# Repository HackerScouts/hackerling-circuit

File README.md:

hackerling-circuit
==================

Development in this Repo is closed.. continued work on the Hackerling Circuit can be found -> https://github.com/CuriosityHacked/hackerling-circuit

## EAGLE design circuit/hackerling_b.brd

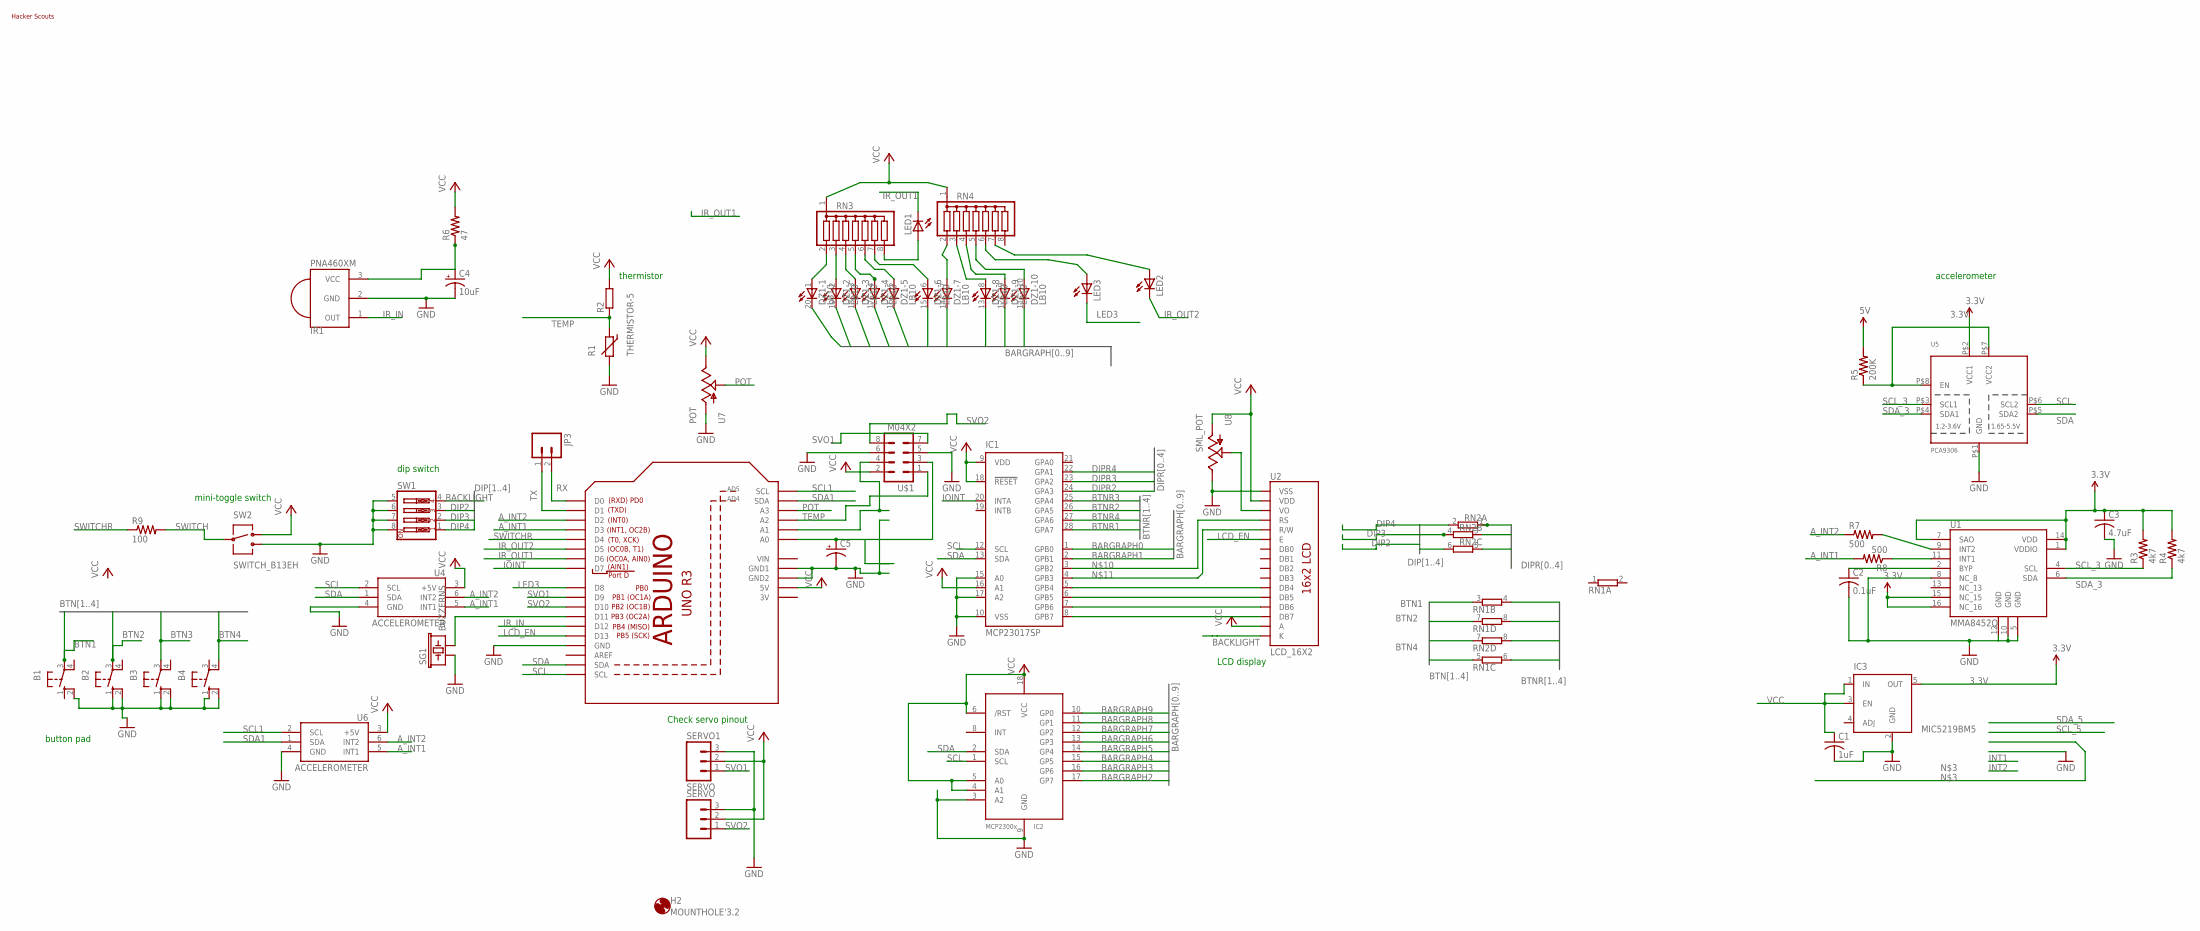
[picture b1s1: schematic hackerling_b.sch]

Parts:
B1, B2, B3, B4: SWITCH_BCF-4000; SWITCH_B3F-4000
C1: 1uF; C0603K
C2: 0.1uF; C0603K
C3: 4.7uF; C0603K
C4: 10uF; CAP_050X075
C5: CPOL-USE5-4; E5-4
DZ1: LB10
H2: MOUNTHOLE'3.2; HOLE_3.2
HACKERSCOUTSLOGO: HS-LOGO; HS-LOGO-SM-NOTEXT
IC1: MCP23017SP; DIL28-3
IC2: MCP2300X/P; DIL18
IC3: MIC5219BM5; SOT23-5
IR1: PNA460XM
JP3: M02LOCK; 1X02_LOCK
LED1, LED2, LED3: LED5MM
R1: THERMISTOR-5; R-5
R2: R-EU_0204/7; 0204/7
R3, R4: 4k7; 0603-RES
R5: 200K; 0603-RES
R6: 47; 0204/7
R7, R8: 500; 0603-RES
R9: 100; 0204/7
RN1, RN2: E4R; SIL8
RN3, RN4: G07R; SIL8
SERVO: M03LOCK; 1X03_LOCK
SERVO1: SERVO; 1X03_LOCK
SG1: BUZZERNS; BUZZER-12MM-NS
SW1: SW_DIP-4; EDG-04
SW2: SWITCH_B13EH
U1: MMA8452Q; QFN-16(5X3)
U2: LCD_16X2
U3: ARDUINOR3-BPLACE
U4, U6: ACCELEROMETER
U5: PCA9306; VSSOP-8
U7: POT; ALS_POT
U8: SML_POT
U$1: M04X2; 2X4

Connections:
3.3V: C3.1, IC3.5 (OUT), R3.2, R4.2, U1.1 (VDDIO), U1.7 (SAO), U1.14 (VDD), U1.15 (NC_15), U1.16 (NC_16), U5.P$2 (VCC1)
3V: U3.3V
A_INT1: R8.2, U3.D3, U4.5 (INT1), U6.5 (INT1)
A_INT2: R7.1, U3.D2, U4.6 (INT2), U6.6 (INT2)
BACKLIGHT: SW1.4, U2.16 (K)
BARGRAPH0: DZ1.20 (C), IC1.1 (GPB0)
BARGRAPH1: DZ1.19 (C), IC1.2 (GPB1)
BARGRAPH2: DZ1.18 (C), IC2.17 (GP7)
BARGRAPH3: DZ1.17 (C), IC2.16 (GP6)
BARGRAPH4: DZ1.16 (C), IC2.15 (GP5)
BARGRAPH5: DZ1.15 (C), IC2.14 (GP4)
BARGRAPH6: DZ1.14 (C), IC2.13 (GP3)
BARGRAPH7: DZ1.13 (C), IC2.12 (GP2)
BARGRAPH8: DZ1.12 (C), IC2.11 (GP1)
BARGRAPH9: DZ1.11 (C), IC2.10 (GP0)
BTN1: B1.3, RN1.3 (1)
BTN2: B2.3, RN1.7 (1)
BTN3: B3.3, RN2.7 (1)
BTN4: B4.4 (P1), RN1.5 (1)
BTNR1: IC1.28 (GPA7), RN1.4 (2)
BTNR2: IC1.26 (GPA5), RN1.8 (2)
BTNR3: IC1.25 (GPA4), RN2.8 (2)
BTNR4: IC1.27 (GPA6), RN1.6 (2)
DIP2: RN2.6 (2), SW1.3
DIP3: RN2.4 (2), SW1.2
DIP4: RN2.2, SW1.1
DIPR2: IC1.24 (GPA3), RN2.5 (1)
DIPR3: IC1.23 (GPA2), RN2.3 (1)
DIPR4: IC1.22 (GPA1), RN2.1
GND: B1.2 (S1), B2.1 (S), B2.2 (S1), B3.1 (S), B3.2 (S1), B4.1 (S), B4.2 (S1), C1.2, C2.2, C3.2, C4.2 (-), C5.-, IC1.10 (VSS), IC1.15 (A0), IC1.17 (A2), IC2.3 (A2), IC2.9 (GND), IC3.2 (GND), IR1.2 (GND), R1.2, SERVO.3, SERVO1.3, SG1.+ (1), SW1.5, SW1.6, SW1.7, SW1.8, SW2.3, U1.5 (GND), U1.8 (NC_8), U1.10 (GND), U1.12 (GND), U2.1 (VSS), U2.B1 (VSS), U3.GND, U3.GND1, U3.GND2, U4.4 (GND), U5.P$1 (GND), U6.4 (GND), U7.P$1 (A), U8.E, U$1.5, U$1.6
IOINT: IC1.20 (INTA), U3.D7
IR_IN: IR1.1 (OUT), U3.D12
IR_OUT1: LED1.K (C), U3.D6
IR_OUT2: LED2.K (C), U3.D5
LCD_EN: U2.6 (E), U3.D13
LED3: LED3.K (C), U3.D8
unnamed: IC1.8 (GPB7), U2.14 (DB7)
unnamed: IC1.7 (GPB6), U2.13 (DB6), U2.B13 (DB6)
unnamed: IC1.6 (GPB5), U2.12 (DB5), U2.B12 (DB5)
unnamed: IC1.5 (GPB4), U2.11 (DB4)
unnamed: R5.1, U5.P$7 (VCC2), U5.P$8 (EN)
unnamed: R7.2, U1.9 (INT2)
unnamed: R8.1, U1.11 (INT1)
unnamed: DZ1.2 (A), RN3.3
unnamed: DZ1.3 (A), RN3.4
unnamed: IC1.3 (GPB2), U2.4 (RS)
unnamed: IC1.4 (GPB3), U2.5 (R/W)
unnamed: LED2.A, RN4.7
unnamed: U2.3 (VO), U8.S
unnamed: SG1.- (2), U3.D11
unnamed: DZ1.7 (A), RN4.2
unnamed: DZ1.6 (A), RN3.7
unnamed: DZ1.1 (A), RN3.2
unnamed: C4.1 (+), IR1.3 (VCC), R6.1
unnamed: LED3.A, RN4.6
unnamed: DZ1.4 (A), RN3.5
unnamed: DZ1.5 (A), RN3.6
unnamed: U3.A1, U$1.4
unnamed: C2.1, U1.2 (BYP)
unnamed: C5.+, U3.A0, U$1.3
unnamed: DZ1.8 (A), RN4.3
unnamed: DZ1.9 (A), RN4.4
unnamed: DZ1.10 (A), RN4.5
unnamed: LED1.A, RN3.8
POT: U3.A3, U7.P$2 (S)
RX: JP3.2, U3.D0
SCL: IC1.12 (SCL), IC2.1 (SCL), U3.SCL, U4.2 (SCL), U5.P$6 (SCL2)
SCL1: U3.A5 (SCL), U6.2 (SCL)
SCL_3: R3.1, U1.4 (SCL), U5.P$3 (SCL1)
SDA: IC1.13 (SDA), IC2.2 (SDA), U3.SDA, U4.1 (SDA), U5.P$5 (SDA2)
SDA1: U3.A4 (SDA), U6.1 (SDA)
SDA_3: R4.1, U1.6 (SDA), U5.P$4 (SDA1)
SVO1: SERVO1.1, U3.D9, U$1.7
SVO2: SERVO.1, U3.D10, U$1.8
SWITCH: R9.2, SW2.2
SWITCHR: R9.1, U3.D4
TEMP: R1.1, R2.1, U3.A2, U$1.1
TX: JP3.1, U3.D1
VCC: C1.1, IC1.9 (VDD), IC1.16 (A1), IC1.18 (!RESET), IC2.4 (A1), IC2.5 (A0), IC2.6 (/RST), IC2.18 (VCC), IC3.1 (IN), IC3.3 (EN), R2.2, R5.2, R6.2, RN3.1, RN4.1, SERVO.2, SERVO1.2, SW2.1, U2.2 (VDD), U2.15 (A), U2.B2 (VDD), U3.5V, U4.3 (+5V), U6.3 (+5V), U7.P$3 (E), U8.A, U$1.2
VIN: U3.VIN

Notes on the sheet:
mini-toggle switch
thermistor
dip switch
LCD display
button pad
accelerometer
Check servo pinout

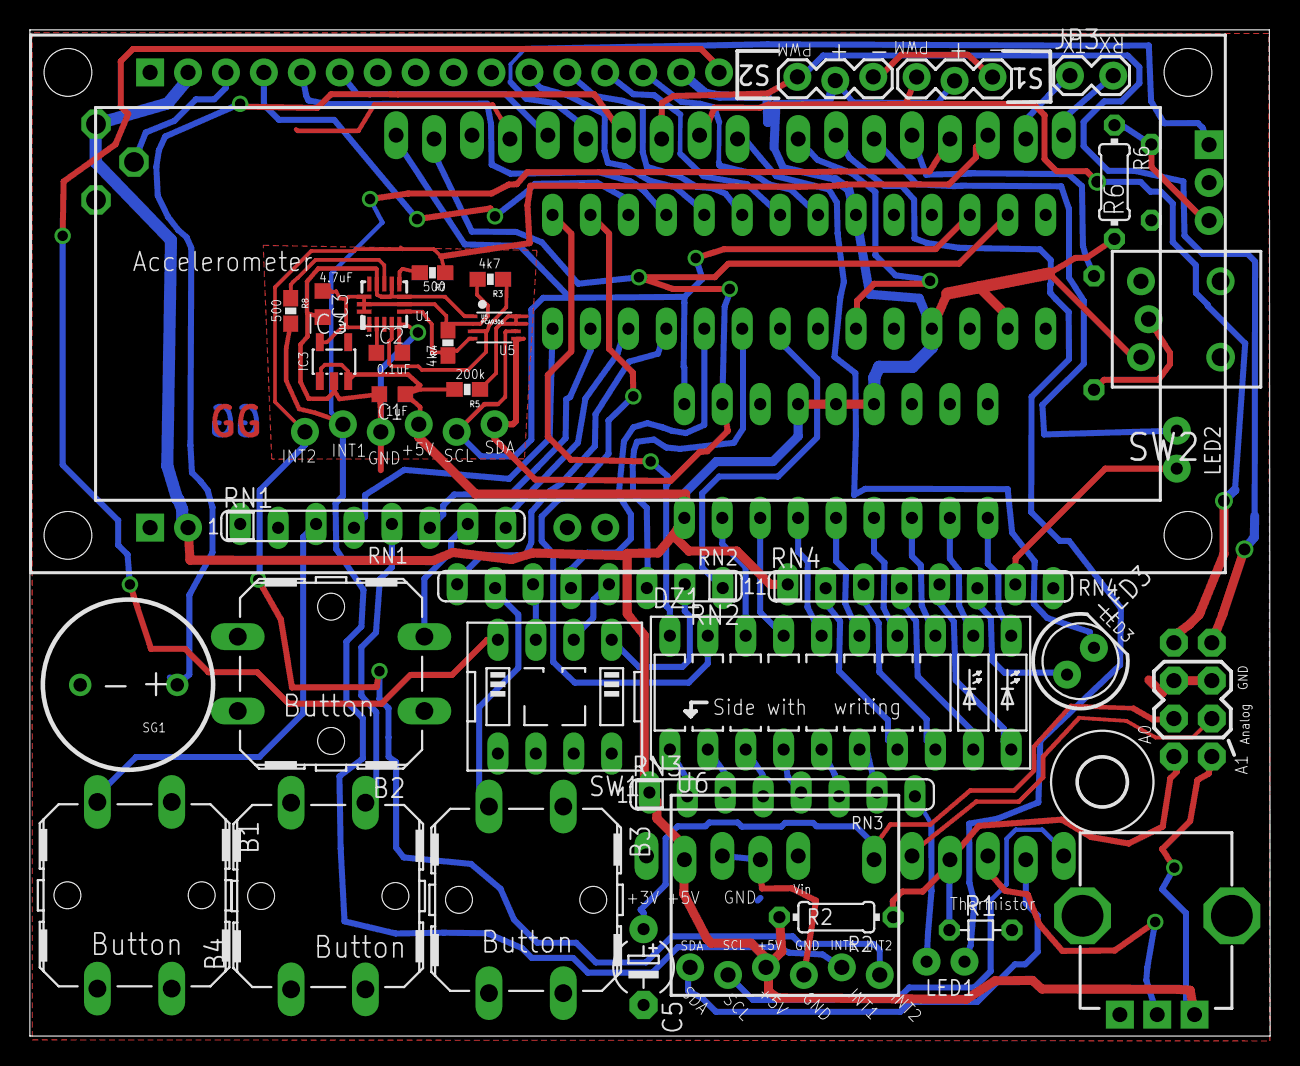
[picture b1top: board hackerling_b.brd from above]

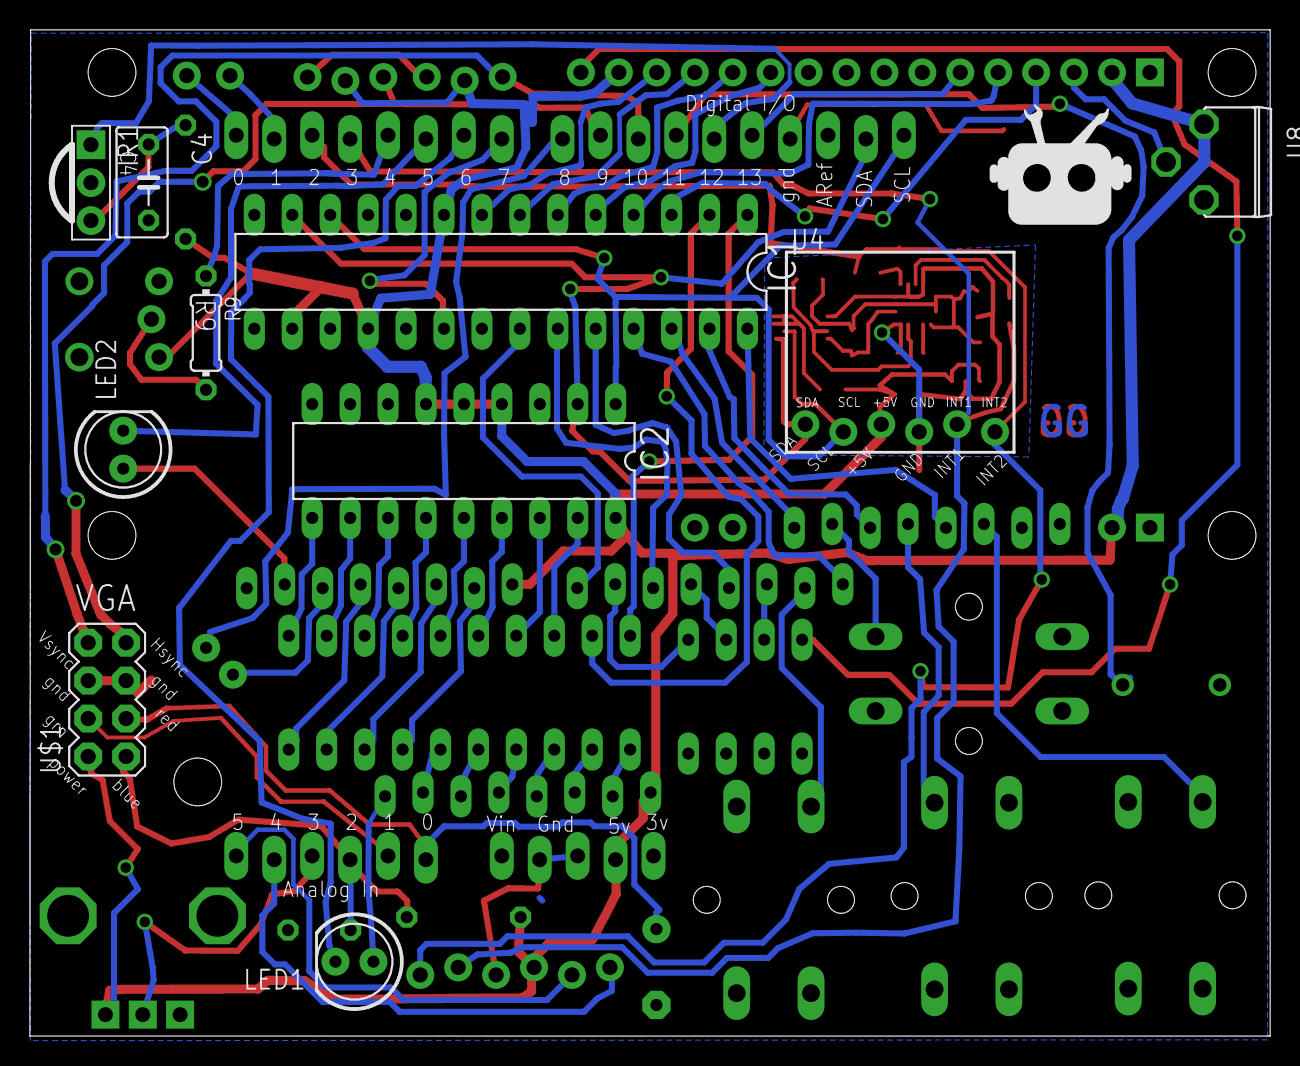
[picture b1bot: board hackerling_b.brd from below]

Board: 2 copper layers, 83.1 x 67.4 mm, 47 parts (11 on the bottom side), 78 nets.

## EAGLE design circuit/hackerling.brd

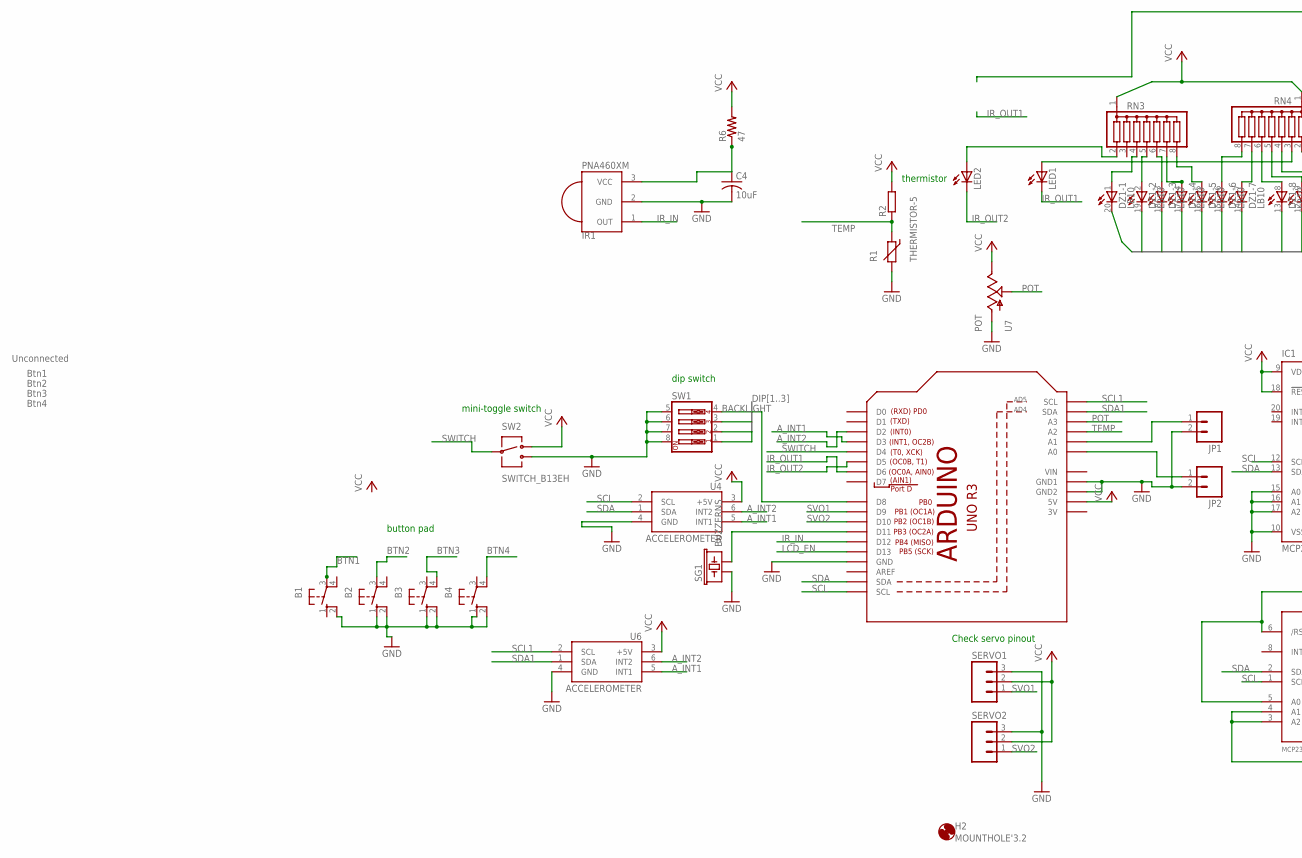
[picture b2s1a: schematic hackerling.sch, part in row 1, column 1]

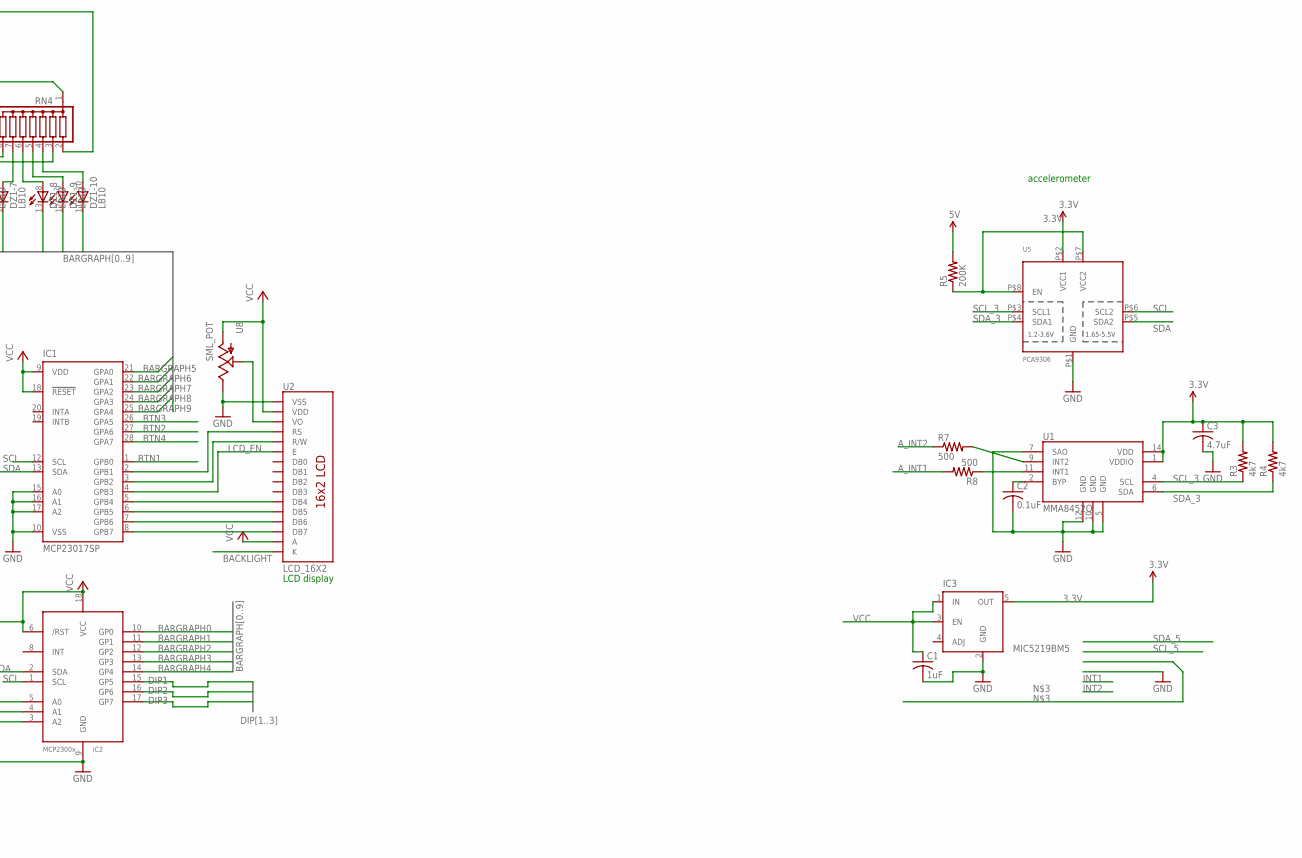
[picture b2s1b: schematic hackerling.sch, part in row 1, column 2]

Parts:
B1, B2, B3, B4: SWITCH_BCF-4000; SWITCH_B3F-4000
C1: 1uF; C0603K
C2: 0.1uF; C0603K
C3: 4.7uF; C0603K
C4: 10uF; C050-050X075
DZ1: LB10
H2: MOUNTHOLE'3.2; HOLE_3.2
IC1: MCP23017SP; DIL28-3
IC2: MCP2300X/P; DIL18
IC3: MIC5219BM5; SOT23-5
IR1: PNA460XM
JP1, JP2: M02LOCK; 1X02_LOCK
LED1, LED2: LED5MM
R1: THERMISTOR-5; R-5
R2: R-EU_0204/7; 0204/7
R3, R4: 4k7; 0603-RES
R5: 200K; 0603-RES
R6: 47; 0204/7
R7, R8: 500; 0603-RES
RN3, RN4: G07R; SIL8
SERVO1, SERVO2: M03LOCK; 1X03_LOCK
SG1: BUZZERNS; BUZZER-12MM-NS
SW1: SW_DIP-4; EDG-04
SW2: SWITCH_B13EH
U1: MMA8452Q; QFN-16(5X3)
U2: LCD_16X2
U3: ARDUINOR3-BPLACE
U4, U6: ACCELEROMETER
U5: PCA9306; VSSOP-8
U7: POT; ALS_POT
U8: SML_POT

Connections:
3.3V: C3.1, IC3.5 (OUT), R3.2, R4.2, U1.1 (VDDIO), U1.14 (VDD), U5.P$2 (VCC1)
3V: U3.3V
A_INT1: R8.2, U3.D3, U4.5 (INT1), U6.5 (INT1)
A_INT2: R7.1, U3.D2, U4.6 (INT2), U6.6 (INT2)
BACKLIGHT: SW1.4, U2.16 (K), U3.D8
BARGRAPH0: DZ1.20 (C), IC2.10 (GP0)
BARGRAPH1: DZ1.19 (C), IC2.11 (GP1)
BARGRAPH2: DZ1.18 (C), IC2.12 (GP2)
BARGRAPH3: DZ1.17 (C), IC2.13 (GP3)
BARGRAPH4: DZ1.16 (C), IC2.14 (GP4)
BARGRAPH5: DZ1.15 (C), IC1.21 (GPA0)
BARGRAPH6: DZ1.14 (C), IC1.22 (GPA1)
BARGRAPH7: DZ1.13 (C), IC1.23 (GPA2)
BARGRAPH8: DZ1.12 (C), IC1.24 (GPA3)
BARGRAPH9: DZ1.11 (C), IC1.25 (GPA4)
BTN1: B1.3, IC1.1 (GPB0)
BTN2: B2.3, IC1.27 (GPA6)
BTN3: B3.4 (P1), IC1.26 (GPA5)
BTN4: B4.4 (P1), IC1.28 (GPA7)
DIP1: IC2.15 (GP5), SW1.1
DIP2: IC2.16 (GP6), SW1.2
DIP3: IC2.17 (GP7), SW1.3
GND: B1.2 (S1), B2.1 (S), B2.2 (S1), B3.1 (S), B3.2 (S1), B4.1 (S), B4.2 (S1), C1.2, C2.2, C3.2, C4.2, IC1.10 (VSS), IC1.15 (A0), IC1.16 (A1), IC1.17 (A2), IC2.3 (A2), IC2.4 (A1), IC2.9 (GND), IC3.2 (GND), IR1.2 (GND), JP1.2, JP2.2, R1.2, SERVO1.3, SERVO2.3, SG1.+ (1), SW1.5, SW1.6, SW1.7, SW1.8, SW2.3, U1.5 (GND), U1.7 (SAO), U1.10 (GND), U1.12 (GND), U2.1 (VSS), U2.B1 (VSS), U3.GND, U3.GND1, U3.GND2, U4.4 (GND), U5.P$1 (GND), U6.4 (GND), U7.P$1 (A), U8.E
IR_IN: IR1.1 (OUT), U3.D12
IR_OUT1: LED1.K (C), U3.D6
IR_OUT2: LED2.K (C), U3.D5
LCD_EN: IC1.4 (GPB3), U2.6 (E), U3.D13
unnamed: IC1.8 (GPB7), U2.14 (DB7)
unnamed: IC1.7 (GPB6), U2.13 (DB6), U2.B13 (DB6)
unnamed: IC1.6 (GPB5), U2.12 (DB5), U2.B12 (DB5)
unnamed: IC1.5 (GPB4), U2.11 (DB4)
unnamed: R5.1, U5.P$7 (VCC2), U5.P$8 (EN)
unnamed: R7.2, U1.9 (INT2)
unnamed: R8.1, U1.11 (INT1)
unnamed: IC1.2 (GPB1), U2.4 (RS)
unnamed: IC1.3 (GPB2), U2.5 (R/W)
unnamed: LED2.A, RN3.2
unnamed: U2.3 (VO), U8.S
unnamed: SG1.- (2), U3.D11
unnamed: LED1.A, RN4.3
unnamed: DZ1.2 (A), RN3.5
unnamed: DZ1.1 (A), RN3.4
unnamed: C4.1, IR1.3 (VCC), R6.1
unnamed: DZ1.3 (A), RN3.6
unnamed: DZ1.4 (A), RN3.7
unnamed: DZ1.5 (A), RN3.8
unnamed: DZ1.6 (A), RN4.8
unnamed: JP1.1, U3.A1
unnamed: C2.1, U1.2 (BYP)
unnamed: JP2.1, U3.A0
unnamed: DZ1.7 (A), RN4.7
unnamed: DZ1.8 (A), RN4.6
unnamed: DZ1.9 (A), RN4.5
unnamed: DZ1.10 (A), RN4.4
POT: U3.A3, U7.P$2 (S)
SCL: IC1.12 (SCL), IC2.1 (SCL), U3.SCL, U4.2 (SCL), U5.P$6 (SCL2)
SCL1: U3.A5 (SCL), U6.2 (SCL)
SCL_3: R3.1, U1.4 (SCL), U5.P$3 (SCL1)
SDA: IC1.13 (SDA), IC2.2 (SDA), U3.SDA, U4.1 (SDA), U5.P$5 (SDA2)
SDA1: U3.A4 (SDA), U6.1 (SDA)
SDA_3: R4.1, U1.6 (SDA), U5.P$4 (SDA1)
SVO1: SERVO1.1, U3.D9
SVO2: SERVO2.1, U3.D10
SWITCH: SW2.2, U3.D4
TEMP: R1.1, R2.1, U3.A2
VCC: C1.1, IC1.9 (VDD), IC1.18 (!RESET), IC2.5 (A0), IC2.6 (/RST), IC2.18 (VCC), IC3.1 (IN), IC3.3 (EN), R2.2, R5.2, R6.2, RN3.1, RN4.1, SERVO1.2, SERVO2.2, SW2.1, U2.2 (VDD), U2.15 (A), U2.B2 (VDD), U3.5V, U4.3 (+5V), U6.3 (+5V), U7.P$3 (E), U8.A
VIN: U3.VIN

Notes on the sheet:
mini-toggle switch
thermistor
dip switch
LCD display
button pad
accelerometer
Check servo pinout
Unconnected
Btn1
Btn2
Btn3
Btn4

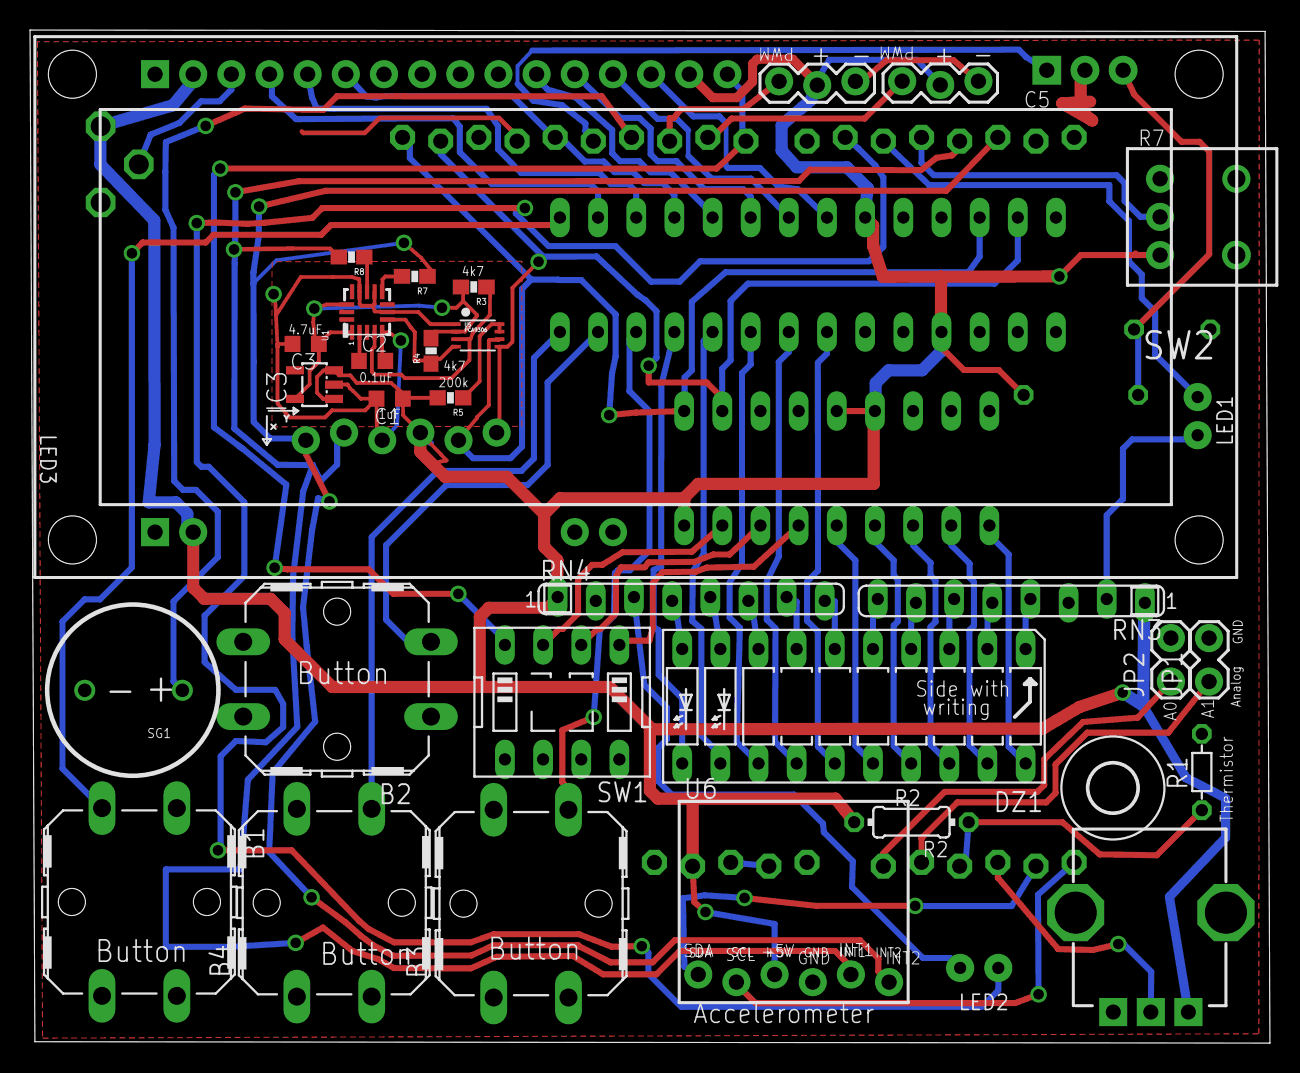
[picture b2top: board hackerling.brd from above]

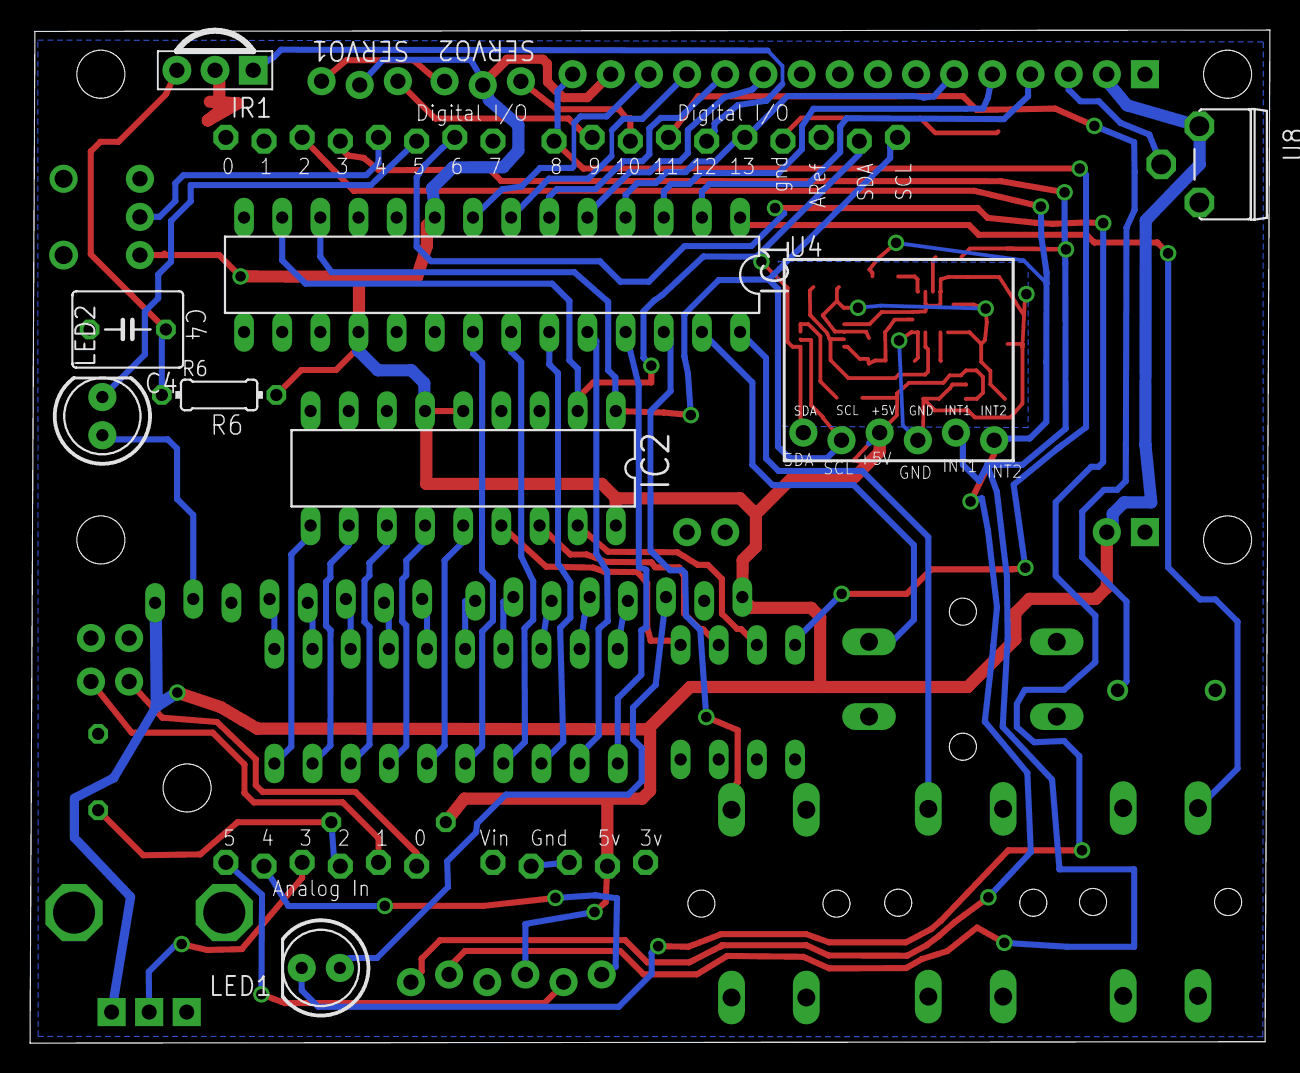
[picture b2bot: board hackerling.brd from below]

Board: 2 copper layers, 82.5 x 67.4 mm, 41 parts (9 on the bottom side), 65 nets.

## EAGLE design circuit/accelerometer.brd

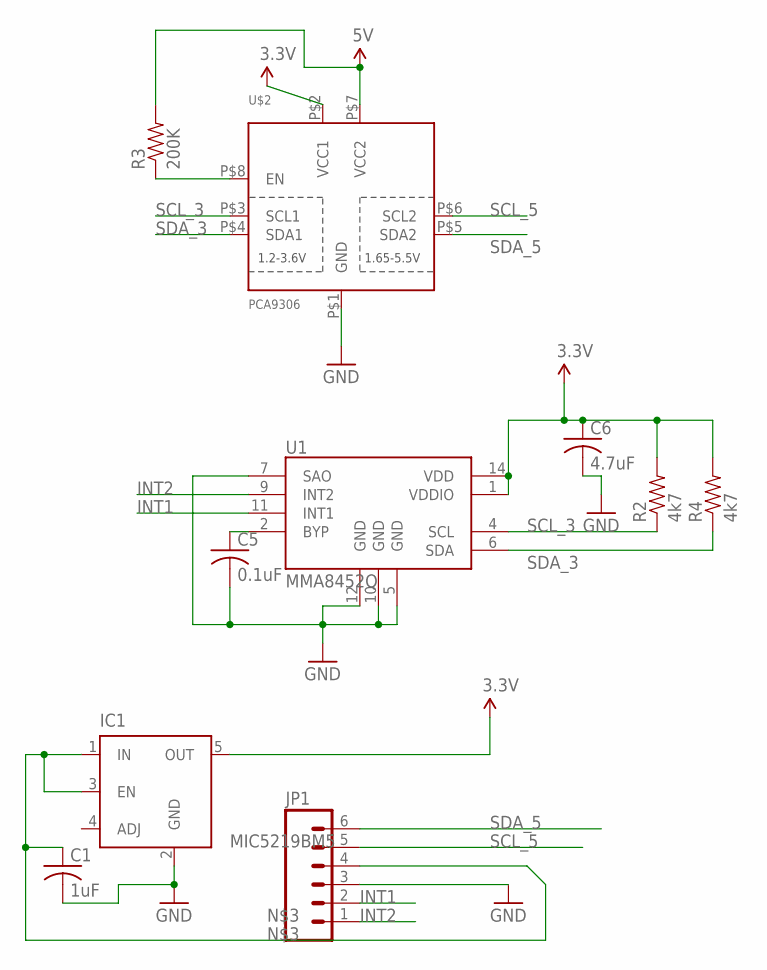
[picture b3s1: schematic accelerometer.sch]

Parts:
C1: 1uF; C0603K
C5: 0.1uF; C0603K
C6: 4.7uF; C0603K
IC1: MIC5219BM5; SOT23-5
JP1: M06LOCK; 1X06_LOCK
R2, R4: 4k7; 0603-RES
R3: 200K; 0603-RES
U1: MMA8452Q; QFN-16(5X3)
U$2: PCA9306; VSSOP-8

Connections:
3.3V: C6.1, IC1.5 (OUT), R2.2, R4.2, U1.1 (VDDIO), U1.14 (VDD), U$2.P$2 (VCC1)
5V: R3.2, U$2.P$7 (VCC2)
GND: C1.2, C5.2, C6.2, IC1.2 (GND), JP1.3, U1.5 (GND), U1.7 (SAO), U1.10 (GND), U1.12 (GND), U$2.P$1 (GND)
INT1: JP1.2, U1.11 (INT1)
INT2: JP1.1, U1.9 (INT2)
unnamed: C5.1, U1.2 (BYP)
unnamed: C1.1, IC1.1 (IN), IC1.3 (EN), JP1.4
unnamed: R3.1, U$2.P$8 (EN)
SCL_3: R2.1, U1.4 (SCL), U$2.P$3 (SCL1)
SCL_5: JP1.5, U$2.P$6 (SCL2)
SDA_3: R4.1, U1.6 (SDA), U$2.P$4 (SDA1)
SDA_5: JP1.6, U$2.P$5 (SDA2)

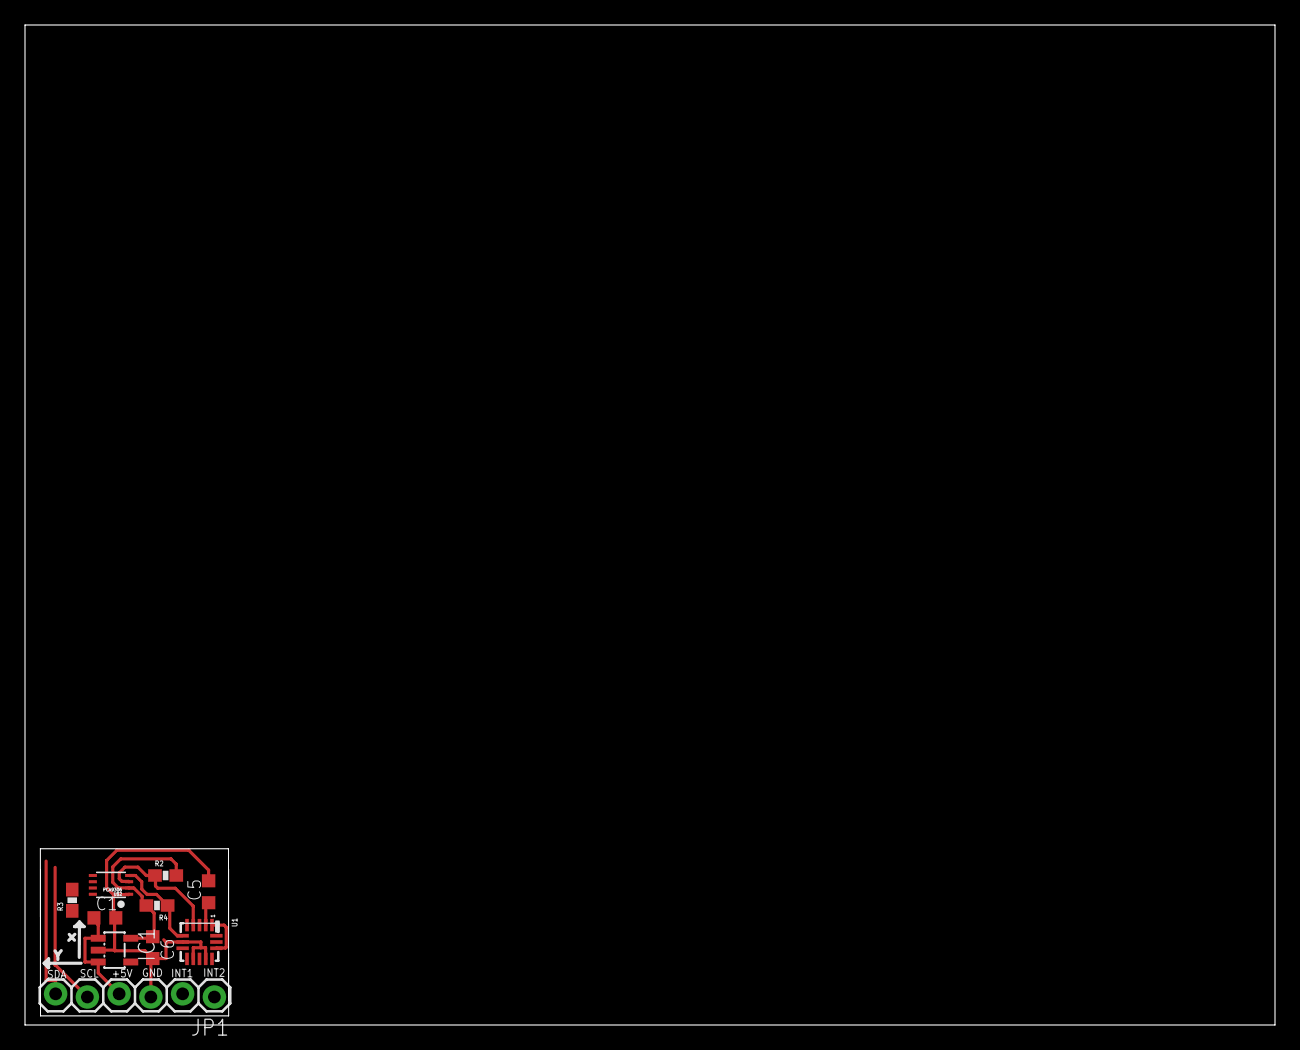
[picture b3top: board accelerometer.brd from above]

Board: 2 copper layers, 100.0 x 80.0 mm, 10 parts (0 on the bottom side), 12 nets.

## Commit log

2012-11-28 initial files and structure
2012-11-28 Created and added gitignore file
2012-11-28 adding BOM
2012-11-28 adding arduino UNO eagle files
2012-11-28 adding arduino UNO schematic pdf
2012-11-29 adding our own eagle library
2012-11-30 adding accelerometer, as a library item, and arranged the circuit layout in a possibly optimal pattern
2012-12-01 arranging the hackerling circuit, added accelerometer layout
2012-12-01 still arranging, about to rotate and shift parts
2012-12-05 circuit state as of barebones order BOM is out of date still.... Just copied hackerling_a back to hackerling.
2012-12-05 adding instruction steps
2012-12-07 fixing a few bugs, updating bom
2012-12-10 adding lots of documentation in the reference layer
2012-12-11 Added spec sheet for MCP23008
2012-12-12 changing accelerometer, adding hooked up address pins
2012-12-23 adding adafruit libs to software folder
2012-12-24 hadding libs
2012-12-24 re-arranged directories to that they work with arduino structure. CylonBarGraph compiles and makes LEDs blink.
2012-12-25 old changes to circuit adding design docs adding libraries for new chips
2012-12-26 finished MCP23008 started IR communication library
2012-12-27 IR_COM in debug mode. very messy
2012-12-27 tested LCD, works added library to test with - library needs cleaning made some minor changes to the board, removed rx, tx connections
2012-12-27 tested MCP23008, works changed buttons to connect to MCP23017 rerouted stuff
2012-12-29 circuit state upon submit of version 1.0
2012-12-31 resubmitting circuit version 1.1 was held for drill overlap modified board slightly, mostly in soldermask to improve readability the ir reciever shifted, and moved a few vias.
2013-01-07 documenting updated values in eagle files filled out BOM writing installation instructions
2013-01-07 updated instructions
2013-01-08 adding demos
2013-01-13 adding examples for assembly steps
2013-01-13 staging the hackerling circuit class
2013-01-21 reorganizing example files
2013-01-22 updated lcd lib added more demos upgraded lcd demo to include HS
2013-01-25 dumping in all the programs I've been using
2013-01-27 IR working with shield and LCD libs added demo that records ir signal and sends it back
2013-01-29 updated hackerling shield to include lcd and IR
2013-02-04 updating libraries to be compatible with new ir_com delay func
2013-02-04 changing delay
2013-02-05 tweaking the demos
2013-02-26 added pouch and enclosure. they should be updated soon.
2013-04-10 power change to accelerometer section
2013-04-10 removing optional components
2013-04-10 updating design files
2013-04-11 adding resistors to interrupt
2013-04-15 before moving pins around
2013-04-15 added updated board hackerling_b. It contains the changes that were needed from v1.1 to v1.2 the board will be merged back into the main board after approval.
2013-04-18 made silkscreen and some cosmetic changes
2013-04-25 changes made for version 1.2. ordered boards.
2013-07-12 adding version 1.2 changes.
2014-01-27 adding version 1.3 schematics
2014-02-12 Update MMA8452Q_Example2.pde
    flipping the address bit, which which changed in version 1.2
2014-02-12 Update MMA8452Q_Example.pde
    flipping the address bit, which changed in version 1.2
2014-03-02 updating BOM
2014-08-07 Adding basic chat system to the hackerling circuit.
    Added a library in software/libraries/Chat_System.
    Example of usage in software/projects/chat_system/chat_system.ino
